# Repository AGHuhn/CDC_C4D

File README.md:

# CDC_C4D

This repository provides building instructions and software to build and operate a capacitance-to-digital converter-based capacitively coupled contactless conductivity (C4D) for capillary electrophoresis.
The setup has the following features:
- performance comparable to other C4Ds
- automated measurements
- lightweight detection head
- wireless data transmission
- battery-powerd setups 
- multi-detector setups
- trigger module for popular commercial CE-Systems

All important information for building and operating is included in the CDCD_Manual.pdf 

The Folder [Hardware](https://github.com/AGHuhn/CDC_C4D/tree/main/Hardware) provides:
- A list of all needed parts
- Eagle Files for detection head (scheme and PCB design)
- Eagle Files for supply unit (scheme and PCB design)
- Eagle File for a Trigger Module for an Agilent CE 7100 (scheme and PCB design)
- Inventor Files for 3D printed case for supply unit of a detection unit

The Folder [Arduino](https://github.com/AGHuhn/CDC_C4D/tree/main/Arduino) contains the Firmware for the Arduino Nanos used

The Folder [Software](https://github.com/AGHuhn/CDC_C4D/tree/main/Software) contains a python 3 script with GUI (CDC_Viewer55.pyw) to acquire the data provides by the detectors 

Publication in [Electrophoresis](https://onlinelibrary.wiley.com/journal/15222683):
Graf, H.G., Rudisch, B.M., Manegold, J. and Huhn, C. (2021), Advancements in capacitance‐to‐digital converter‐based C4D technology for detection in capillary electrophoresis using amplified excitation voltages and comparison to classical and open‐source C4Ds. ELECTROPHORESIS. https://doi.org/10.1002/elps.202000394

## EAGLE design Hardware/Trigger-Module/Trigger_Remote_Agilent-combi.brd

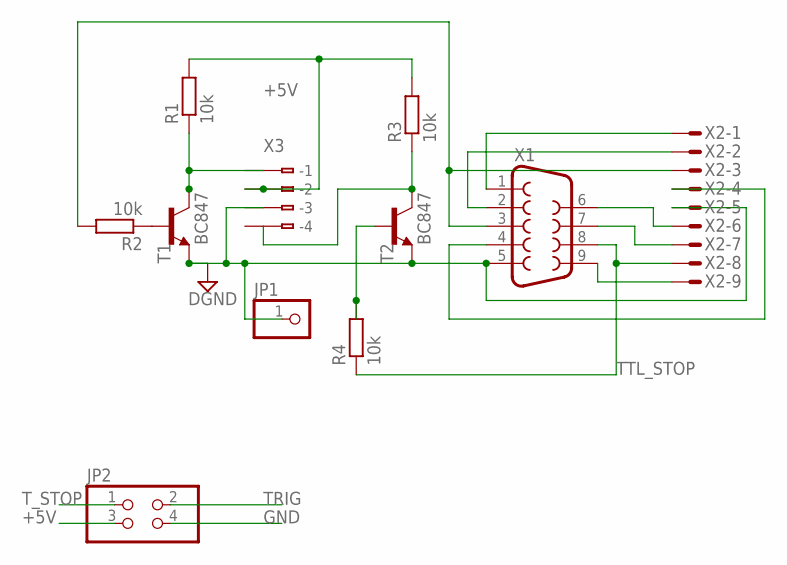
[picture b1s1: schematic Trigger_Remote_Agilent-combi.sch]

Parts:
JP1: PINHD-1X1; 1X01
JP2: PINHD-2X2; 2X02
R1, R2, R3, R4: 10k; M0805
T1, T2: BC847; SOT23
X1: F09HP
X2: M09HPS; M09HP
X3: 233-504

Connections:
+5V: JP2.3, R1.2, R3.2, X3.A2 (-2), X3.B2 (B-2)
GND: JP1.1, JP2.4, T1.2 (E), T2.2 (E), X1.5, X2.5, X3.A3 (-3)
unnamed: X1.1, X2.1
unnamed: X1.2, X2.2
unnamed: X1.4, X2.4
unnamed: R2.1, T1.1 (B)
unnamed: X1.9, X2.9
unnamed: X1.7, X2.7
unnamed: X1.6, X2.6
unnamed: R4.2, T2.1 (B)
TRIG: JP2.2, R1.1, T1.3 (C), X3.A1 (-1)
TTLSTART: R2.2, X1.3, X2.3
TTL_STOP: R4.1, X1.8, X2.8
T_STOP: JP2.1, R3.1, T2.3 (C), X3.A4 (-4)

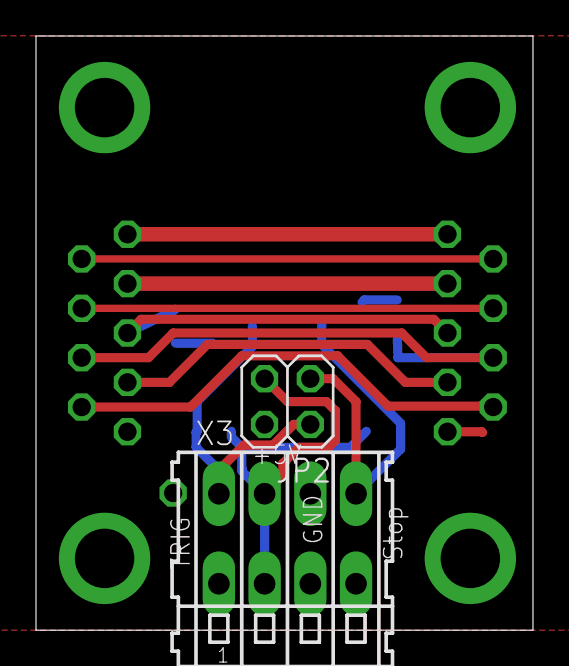
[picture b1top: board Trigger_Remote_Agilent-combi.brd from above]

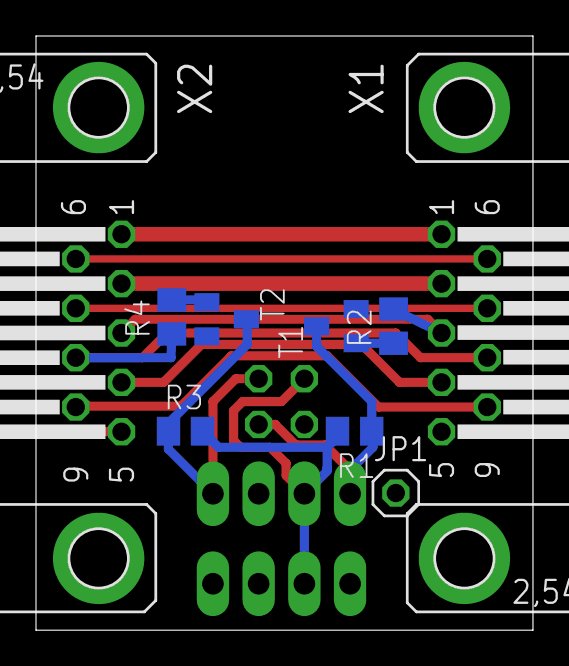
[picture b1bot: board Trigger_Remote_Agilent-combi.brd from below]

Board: 2 copper layers, 27.6 x 33.0 mm, 11 parts (9 on the bottom side), 14 nets.

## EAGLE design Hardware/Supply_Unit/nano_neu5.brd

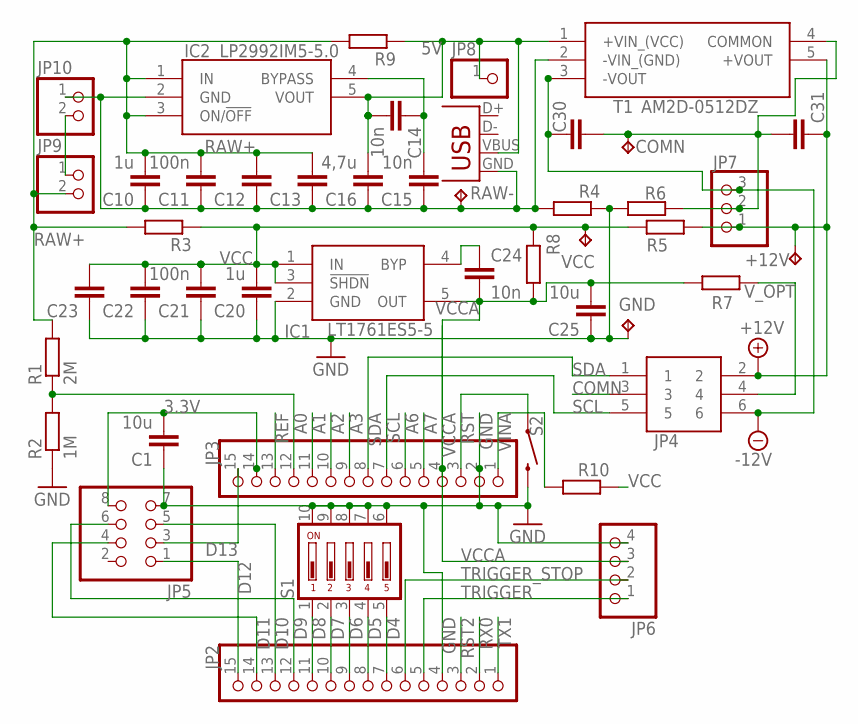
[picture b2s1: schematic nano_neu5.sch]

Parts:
+12V: TESTPAD_TPTP09SQ; TESTPAD_TP09SQ
C1, C25: 10u; RCL_C0805K
C10, C20: 1u; RCL_C0805K
C11, C21: 100n; RCL_C0805K
C12, C13, C22, C23, C30, C31: RCL_C-EUC1206K; RCL_C1206K
C14, C15, C24: 10n; RCL_C0805K
C16: 4,7u; RCL_C0805K
COMN: TESTPAD_TPTP09SQ; TESTPAD_TP09SQ
GND: TESTPAD_TPTP09SQ; TESTPAD_TP09SQ
IC1: LT1761ES5-5; SAMACSYS_PARTS_SOT95P280X100-5N
IC2: LP2992IM5-5.0; SAMACSYS_PARTS_SOT95P280X145-5N
JP2, JP3: ADAFRUIT_PINHD-1X15-CB; ADAFRUIT_1X15-CB
JP4: SAMACSYS_PARTS_FTSH-103-01-F-D; SAMACSYS_PARTS_FTSH10301FD
JP5: PINHEAD_PINHD-2X4; PINHEAD_2X04
JP6: PINHD-1X4-CB; ADAFRUIT_1X04-CLEANBIG
JP7: ADAFRUIT_PINHD-1X3CB; ADAFRUIT_1X03-CLEANBIG
JP8: PINHEAD_PINHD-1X1; PINHEAD_1X01
JP9, JP10: PINHEAD_PINHD-1X2; PINHEAD_1X02
R1: 2M; RCL_R0805
R2: 1M; RCL_R0805
R3, R4, R5, R6, R7, R8, R9: RCL_R-EU_R0805; RCL_R0805
R10: RCL_R-EU_R0603; RCL_R0603
RAW-: RAW-; TESTPAD_TP09SQ
S1: SWITCH-DIL_219-05; SWITCH-DIL_CTS-219-05
S2: SPARKFUN-SWITCHES_MOMENTARY-SWITCH-SPST-SMD-6.0X3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; SPARKFUN-SWITCHES_TACTILE_SWITCH_SMD_6.0X3.5MM
T1: AM2D-0512DZ; SAMACSYS_PARTS_TMA-0512D
VCC: TESTPAD_TPTP09SQ; TESTPAD_TP09SQ
X1: CON-USB_USB-MB-S

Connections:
3.3V: C1.2, JP3.14, JP5.8
5V: C14.2, C16.2, IC2.5 (VOUT), JP8.1, R9.1, T1.1 (+VIN_(VCC)), X1.VBUS
+12V: +12V.TP, C31.1, JP4.2, JP7.1, R5.2, T1.5 (+VOUT)
-12V: C30.1, JP4.6, JP7.3, T1.3 (-VOUT)
A0: JP3.12, R1.1, R2.2
A1: JP3.11
A2: JP3.10
A3: JP3.9
A6: JP3.6
A7: JP3.5
COMN: C30.2, C31.2, COMN.TP, JP4.3, JP7.2, R6.2, T1.4 (COMMON)
D4: JP2.7, S1.5
D5: JP2.8, S1.4
D6: JP2.9, S1.3
D7: JP2.10, S1.2
D8: JP2.11, S1.1
D9: JP2.12, JP5.6
D10: JP2.13, JP5.5
D11: JP2.14, JP5.4
D12: JP2.15, JP5.1
D13: JP3.15, JP5.3
GND: C1.1, C20.1, C21.1, C22.1, C23.1, C25.1, GND.TP, IC1.2 (GND), JP2.4, JP3.2, JP5.7, JP6.4, R2.1, R4.1, R6.1, S1.6, S1.7, S1.8, S1.9, S1.10, S2.2
unnamed: JP9.1, JP10.2
unnamed: C24.1, IC1.4 (BYP)
unnamed: C14.1, C15.2, IC2.4 (BYPASS)
RAW+: C10.2, C11.2, C12.2, C13.2, IC2.1 (IN), IC2.3 (ON/!OFF), JP9.2, R1.2, R3.2, R9.2
RAW-: C10.1, C11.1, C12.1, C13.1, C15.1, C16.1, IC2.2 (GND), JP10.1, R4.2, RAW-.TP, T1.2 (-VIN_(GND)), X1.GND
REF: JP3.13
RST: JP3.3, S2.1
RST2: JP2.3
RX0: JP2.2
SCL: JP3.7, JP4.5
SDA: JP3.8, JP4.1
TRIGGER: JP2.5, JP6.1
TRIGGER_STOP: JP2.6, JP6.2
TX1: JP2.1
VCC: C20.2, C21.2, C22.2, C23.2, IC1.1 (IN), IC1.3 (!SHDN), R3.1, R5.1, R8.2, R10.1, VCC.TP
VCCA: C24.2, C25.2, IC1.5 (OUT), JP3.4, JP6.3, R7.1, R8.1
VINA: JP3.1, R10.2
V_OPT: JP4.4, R7.2

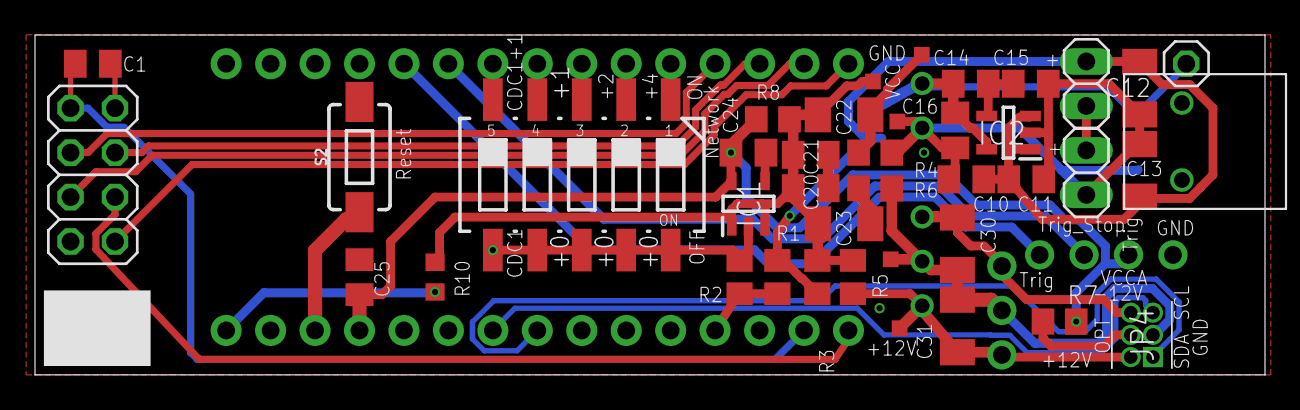
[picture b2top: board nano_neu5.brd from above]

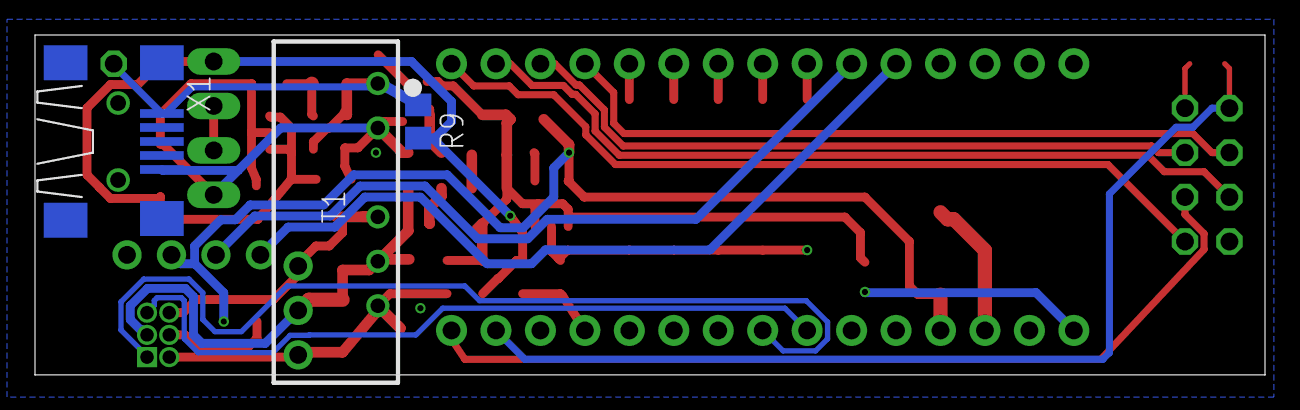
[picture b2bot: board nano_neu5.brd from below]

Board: 2 copper layers, 70.3 x 19.4 mm, 46 parts (3 on the bottom side), 31 nets.

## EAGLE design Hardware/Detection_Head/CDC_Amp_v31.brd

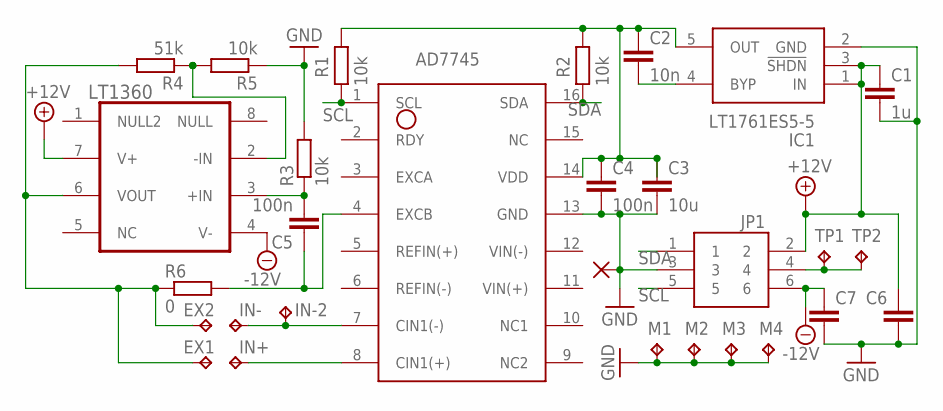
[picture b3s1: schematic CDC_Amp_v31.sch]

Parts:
AD7745: AD7745; AD7745_TSSOP_16
C1: 1u; RCL_C0805
C2: 10n; RCL_C0805
C3: 10u; RCL_C0805
C4, C5: 100n; RCL_C0805
C6, C7: RCL_C-EUC1206; RCL_C1206
EX1, EX2: TESTPAD_TPTP15R; TESTPAD_TP15R
GND: WIREPAD_1,6/0,8
IC1: LT1761ES5-5; SAMACSYS_PARTS_SOT95P280X100-5N
IN+: TESTPAD_TPTP12R; TESTPAD_TP12R
IN-, IN-2: TESTPAD_TPTP12R; TESTPAD_TP12R
JP1: SAMACSYS_PARTS_FTSH-103-01-F-D; SAMACSYS_PARTS_FTSH10301FD
LT1360: LT1360CS8PBF; SO8
M1, M2, M3, M4: TESTPAD_TPTP15R; TESTPAD_TP15R
R1, R2, R3, R5: 10k; RCL_R0805
R4: 51k; RCL_R0805
R6: 0; RCL_R0603
TP1, TP2: TESTPAD_TPTP08SQ; TESTPAD_TP08SQ

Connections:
+12V: C1.1, C6.1, IC1.1 (IN), IC1.3 (!SHDN), JP1.2, LT1360.7 (V+)
-12V: C7.1, JP1.6, LT1360.4 (V-)
EX_IN: AD7745.4 (EXCB), C5.1, R6.2
EX_OUT: EX1.TP, EX2.TP, LT1360.6 (VOUT), R4.2, R6.1
GND: AD7745.13 (GND), C1.2, C3.2, C4.2, C6.2, C7.2, GND.1, IC1.2 (GND), JP1.3, M1.TP, M2.TP, M3.TP, M4.TP, R3.2, R5.1
unnamed: C5.2, LT1360.3 (+IN), R3.1
unnamed: LT1360.2 (-IN), R4.1, R5.2
unnamed: JP1.4, TP1.TP, TP2.TP
unnamed: C2.2, IC1.4 (BYP)
SCL: AD7745.1 (SCL), JP1.5, R1.1
SDA: AD7745.16 (SDA), JP1.1, R2.1
SIGIN: AD7745.8 (CIN1(+)), IN+.TP
SIGIN-: AD7745.7 (CIN1(-)), IN-.TP, IN-2.TP
V_DD: AD7745.14 (VDD), C2.1, C3.1, C4.1, IC1.5 (OUT), R1.2, R2.2

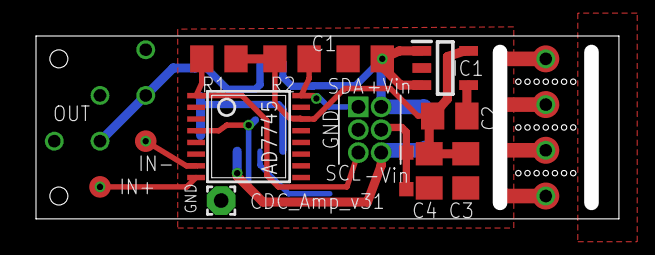
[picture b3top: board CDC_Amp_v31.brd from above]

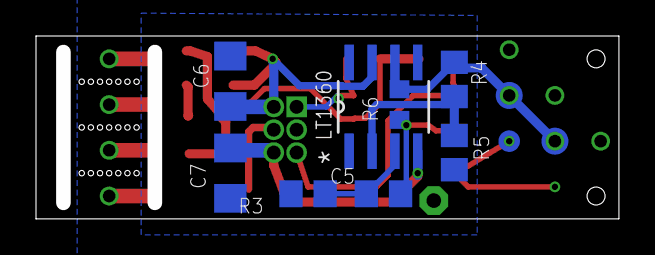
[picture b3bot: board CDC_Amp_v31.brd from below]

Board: 2 copper layers, 32.4 x 10.2 mm, 29 parts (11 on the bottom side), 14 nets.

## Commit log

2021-02-07 Version55
2021-02-27 First Upload
2021-02-27 Trigger modified
2021-02-27 Frist upload
2021-02-27 Manual update
